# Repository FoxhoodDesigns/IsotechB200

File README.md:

# IsotechB200

This github contains the source files of the Amsterdam University of Applied Science innovationlab assignment: B-200 ADC substitution.

With the data in this repository one can recreate the design made for the project and utilize this as a Jump-off point for further development.

# CODE
Contains a sample code showing how to use the Interface with a digital Microcontroller. In this case a regular Arduino UNO.

# EAGLE
Contains Autodesk Eagle board files. Which includes circuit schematic and PCB design.

Note: For possible Eagle library dependancies please view this repository: https://github.com/FoxhoodDesigns/FHD-Libraries

# LTSPICE
Contains the LTSPICE Simulation file used for simulating the analog component of the Interface board

# doc
Contains the PDF and source LaTeX files behind the research. For documentation referencing purposes.

All work presently contained within this repository is made by the original AUAS team:
Chiel Voswijk, Kwint van den Berg and Niels Hupkens.

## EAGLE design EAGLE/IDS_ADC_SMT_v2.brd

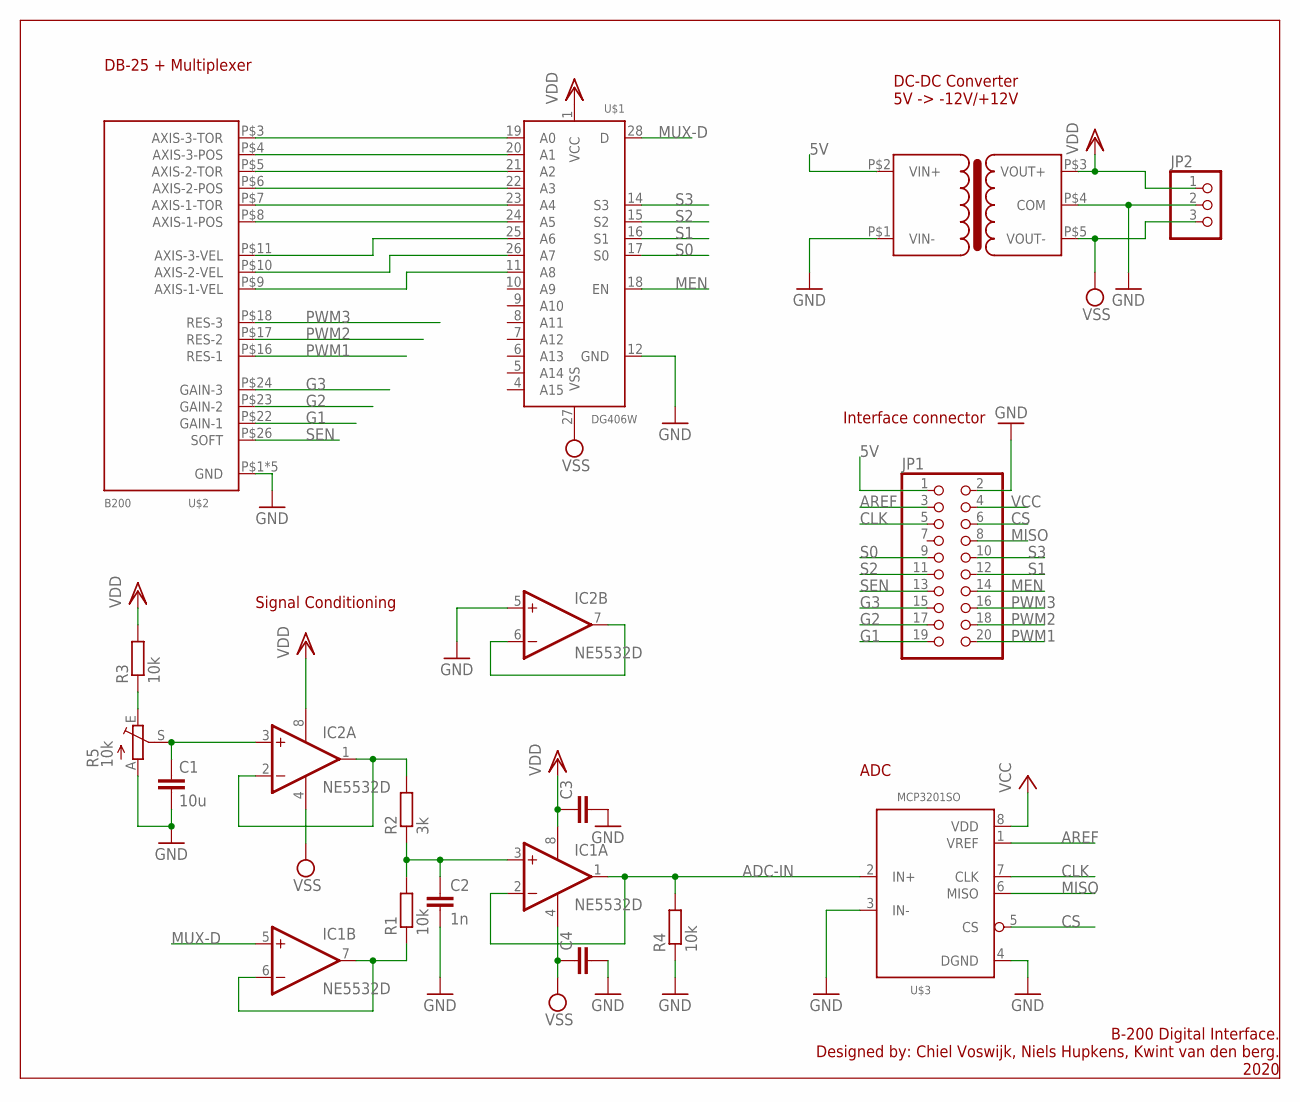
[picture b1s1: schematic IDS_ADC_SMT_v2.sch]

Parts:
C1: 10u; C1210
C2: 1n; C0805
C3, C4: C-EUC0805; C0805
IC1, IC2: NE5532D; SO08
JP1: PINHD-2X10; 2X10
JP2: PINHD-1X3; 1X03
R1, R3, R4: 10k; R0805
R2: 3k; R0805
R5: 10k; RJ9W
U$1: DG406W; SO-28W
U$2: B200; PARALLEL
U$3: MCP3201SO; SO-8
U$4: TRACO-DR-NE; TRACO-DCDC-SIP6

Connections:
5V: JP1.1, U$4.P$2 (VIN+)
ADC-IN: IC1.1 (OUT), IC1.2 (-IN), R4.2, U$3.2 (IN+)
AREF: JP1.3, U$3.1 (VREF)
CLK: JP1.5, U$3.7 (CLK)
CS: JP1.6, U$3.5 (CS)
G1: JP1.19, U$2.P$22 (GAIN-1)
G2: JP1.17, U$2.P$23 (GAIN-2)
G3: JP1.15, U$2.P$24 (GAIN-3)
GND: C1.2, C2.2, C3.2, C4.2, IC2.5 (+IN), JP1.2, JP2.2, R4.1, R5.A, U$1.12 (GND), U$2.P$1 (GND), U$2.P$2 (GND), U$2.P$19 (GND), U$2.P$20 (GND), U$2.P$21 (GND), U$3.3 (IN-), U$3.4 (DGND), U$4.P$1 (VIN-), U$4.P$4 (COM)
MEN: JP1.14, U$1.18 (EN)
MISO: JP1.8, U$3.6 (MISO)
MUX-D: IC1.5 (+IN), U$1.28 (D)
unnamed: IC2.6 (-IN), IC2.7 (OUT)
unnamed: U$1.19 (A0), U$2.P$3 (AXIS-3-TOR)
unnamed: C2.1, IC1.3 (+IN), R1.2, R2.1
unnamed: U$1.20 (A1), U$2.P$4 (AXIS-3-POS)
unnamed: IC1.6 (-IN), IC1.7 (OUT), R1.1
unnamed: U$1.21 (A2), U$2.P$5 (AXIS-2-TOR)
unnamed: IC2.1 (OUT), IC2.2 (-IN), R2.2
unnamed: C1.1, IC2.3 (+IN), R5.S
unnamed: U$1.22 (A3), U$2.P$6 (AXIS-2-POS)
unnamed: U$1.23 (A4), U$2.P$7 (AXIS-1-TOR)
unnamed: U$1.24 (A5), U$2.P$8 (AXIS-1-POS)
unnamed: U$1.25 (A6), U$2.P$11 (AXIS-3-VEL)
unnamed: U$1.26 (A7), U$2.P$10 (AXIS-2-VEL)
unnamed: U$1.11 (A8), U$2.P$9 (AXIS-1-VEL)
unnamed: R3.1, R5.E
PWM1: JP1.20, U$2.P$16 (RES-1)
PWM2: JP1.18, U$2.P$17 (RES-2)
PWM3: JP1.16, U$2.P$18 (RES-3)
S0: JP1.9, U$1.17 (S0)
S1: JP1.12, U$1.16 (S1)
S2: JP1.11, U$1.15 (S2)
S3: JP1.10, U$1.14 (S3)
SEN: JP1.13, U$2.P$26 (SOFT)
VCC: JP1.4, U$3.8 (VDD)
VDD: C3.1, IC1.8 (V+), IC2.8 (V+), JP2.1, R3.2, U$1.1 (VCC), U$4.P$3 (VOUT+)
VSS: C4.1, IC1.4 (V-), IC2.4 (V-), JP2.3, U$1.27 (VSS), U$4.P$5 (VOUT-)

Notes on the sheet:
DB-25 + Multiplexer
DC-DC Converter 5V -> -12V/+12V
ADC
Signal Conditioning
Interface connector
B-200 Digital Interface. Designed by: Chiel Voswijk, Niels Hupkens, Kwint van den berg. 2020

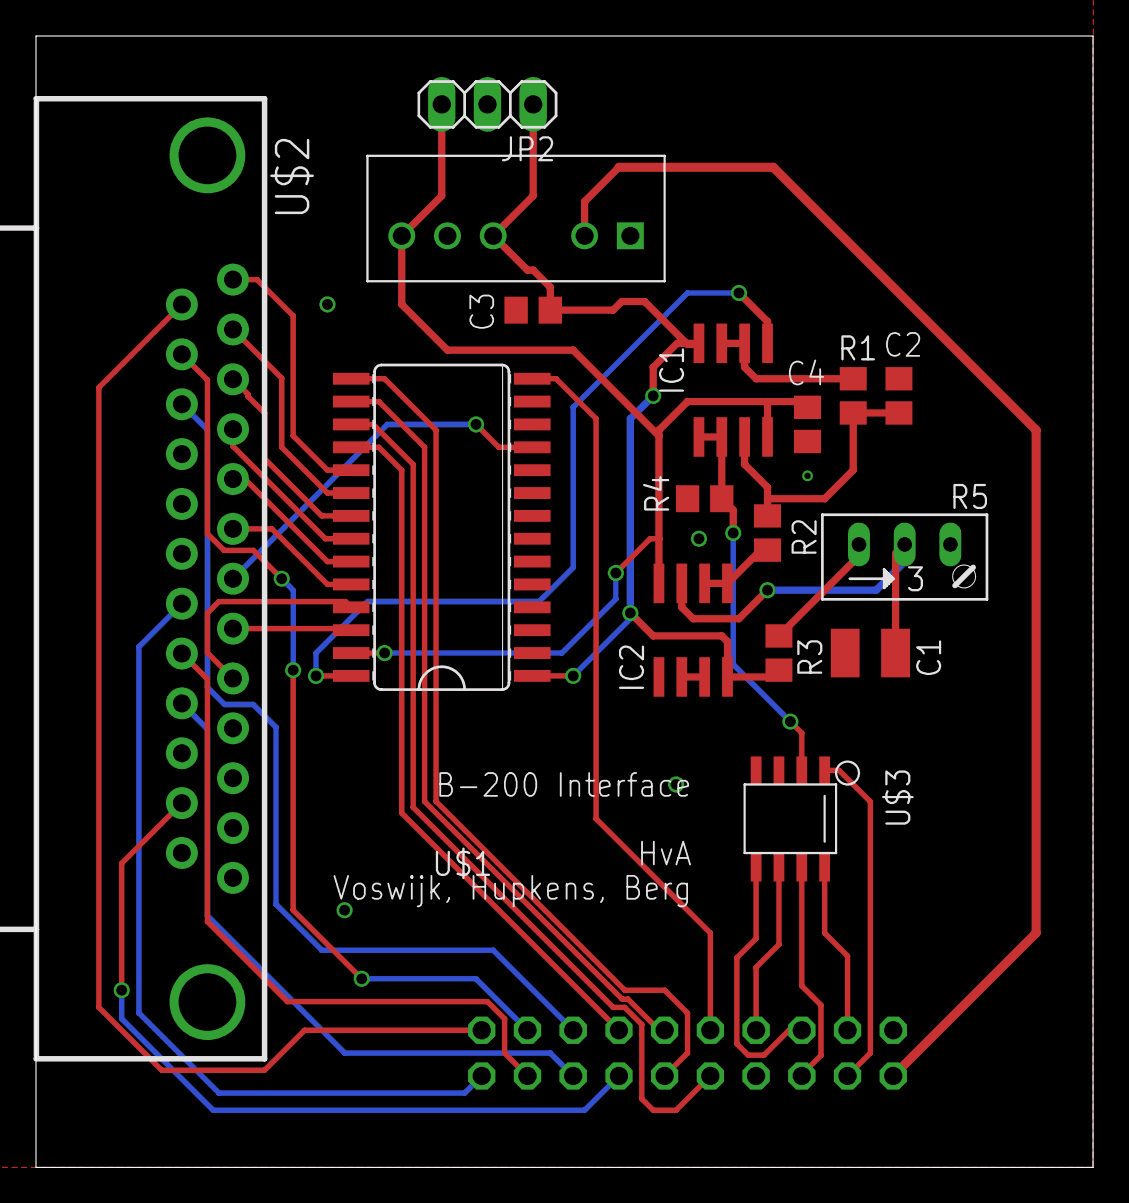
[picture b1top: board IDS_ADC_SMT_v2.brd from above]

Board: 2 copper layers, 58.7 x 62.9 mm, 17 parts (1 on the bottom side), 38 nets.

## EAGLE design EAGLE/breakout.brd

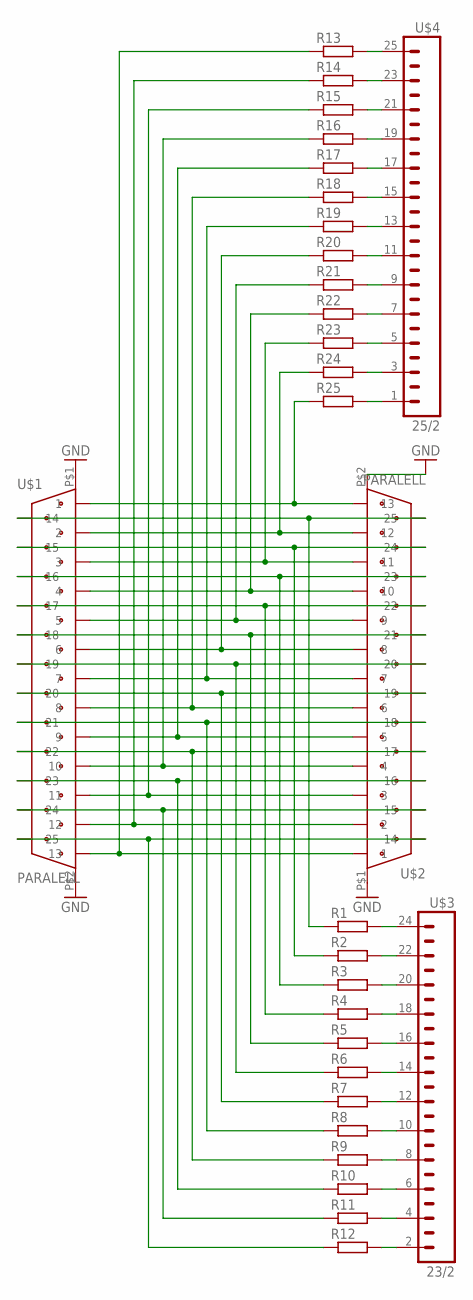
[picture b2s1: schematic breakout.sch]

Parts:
R1, R2, R3, R4, R5, R6, R7, R8, R9, R10, R11, R12, R13, R14, R15, R16, R17, R18, R19, R20, R21, R22, R23, R24, R25: R-EU_0204/7; 0204/7
U$1, U$2: PARALELL; PARALLEL
U$3: 23/2; 1X23
U$4: 25/2; 1X25

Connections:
GND: U$1.P$1, U$1.P$2, U$2.P$1, U$2.P$2
unnamed: R13.1, U$1.P$15 (13), U$2.P$3 (1)
unnamed: R14.1, U$1.P$14 (12), U$2.P$4 (2)
unnamed: R15.1, U$1.P$13 (11), U$2.P$5 (3)
unnamed: R16.1, U$1.P$12 (10), U$2.P$6 (4)
unnamed: R17.1, U$1.P$11 (9), U$2.P$7 (5)
unnamed: R18.1, U$1.P$10 (8), U$2.P$8 (6)
unnamed: R19.1, U$1.P$9 (7), U$2.P$9 (7)
unnamed: R20.1, U$1.P$8 (6), U$2.P$10 (8)
unnamed: R21.1, U$1.P$7 (5), U$2.P$11 (9)
unnamed: R22.1, U$1.P$6 (4), U$2.P$12 (10)
unnamed: R23.1, U$1.P$5 (3), U$2.P$13 (11)
unnamed: R24.1, U$1.P$4 (2), U$2.P$14 (12)
unnamed: R25.1, U$1.P$3 (1), U$2.P$15 (13)
unnamed: R1.2, U$3.24
unnamed: R2.2, U$3.22
unnamed: R3.2, U$3.20
unnamed: R4.2, U$3.18
unnamed: R5.2, U$3.16
unnamed: R6.2, U$3.14
unnamed: R7.2, U$3.12
unnamed: R8.2, U$3.10
unnamed: R9.2, U$3.8
unnamed: R10.2, U$3.6
unnamed: R11.2, U$3.4
unnamed: R12.2, U$3.2
unnamed: R13.2, U$4.25
unnamed: R14.2, U$4.23
unnamed: R15.2, U$4.21
unnamed: R16.2, U$4.19
unnamed: R17.2, U$4.17
unnamed: R18.2, U$4.15
unnamed: R19.2, U$4.13
unnamed: R20.2, U$4.11
unnamed: R21.2, U$4.9
unnamed: R22.2, U$4.7
unnamed: R23.2, U$4.5
unnamed: R24.2, U$4.3
unnamed: R25.2, U$4.1
unnamed: R1.1, U$1.P$16 (14), U$2.P$27 (25)
unnamed: R2.1, U$1.P$17 (15), U$2.P$26 (24)
unnamed: R3.1, U$1.P$18 (16), U$2.P$25 (23)
unnamed: R4.1, U$1.P$19 (17), U$2.P$24 (22)
unnamed: R5.1, U$1.P$20 (18), U$2.P$23 (21)
unnamed: R6.1, U$1.P$21 (19), U$2.P$22 (20)
unnamed: R7.1, U$1.P$22 (20), U$2.P$21 (19)
unnamed: R8.1, U$1.P$23 (21), U$2.P$20 (18)
unnamed: R9.1, U$1.P$24 (22), U$2.P$19 (17)
unnamed: R10.1, U$1.P$25 (23), U$2.P$18 (16)
unnamed: R11.1, U$1.P$26 (24), U$2.P$17 (15)
unnamed: R12.1, U$1.P$27 (25), U$2.P$16 (14)

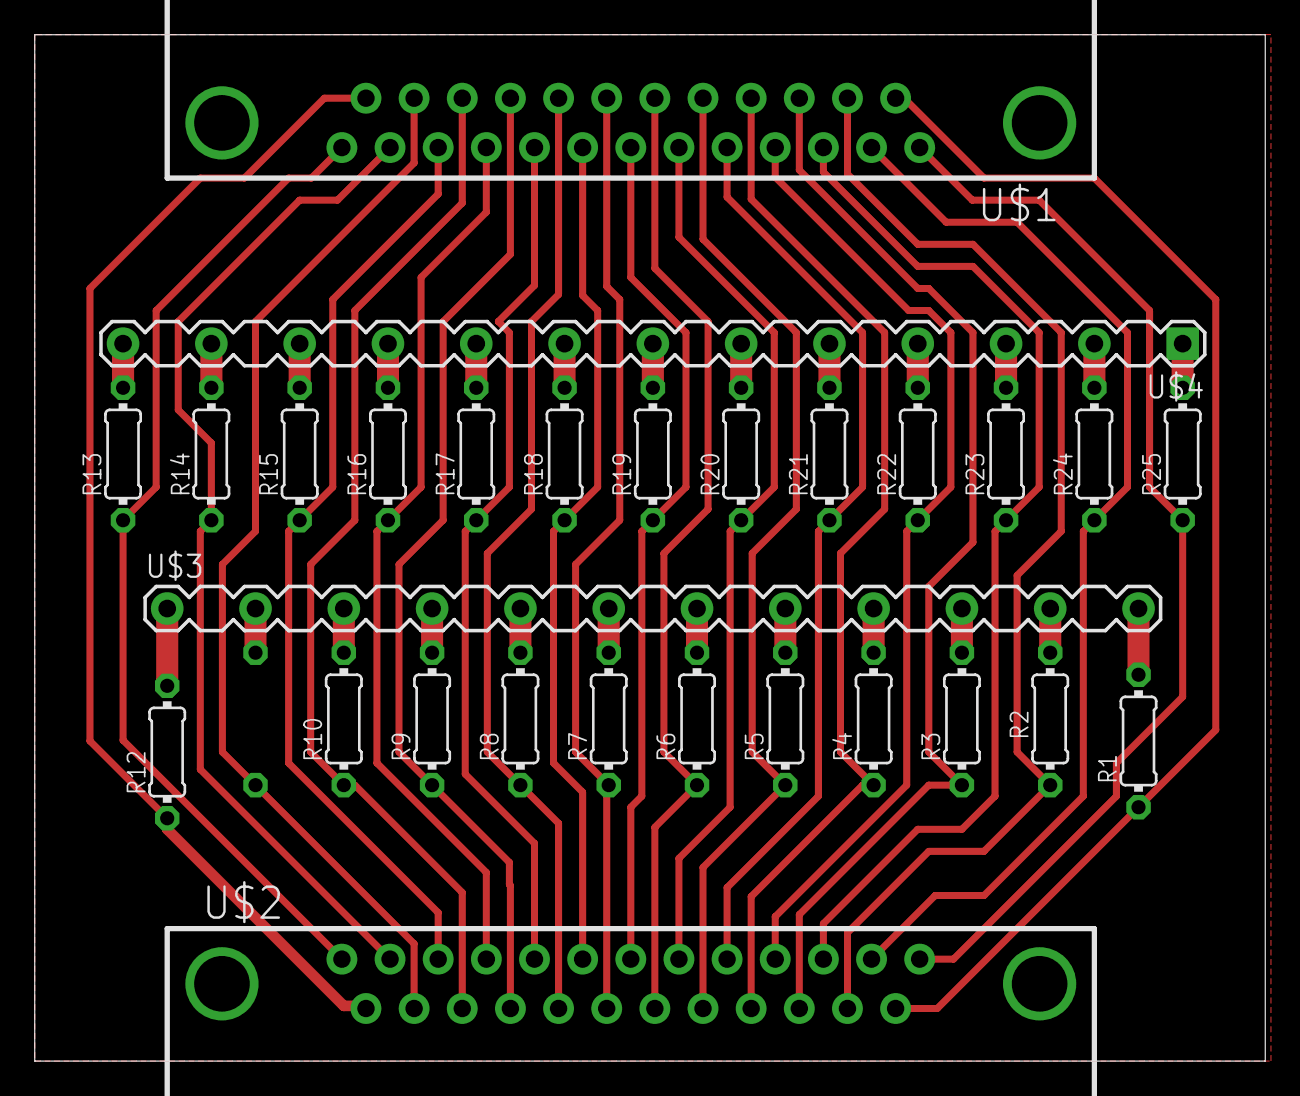
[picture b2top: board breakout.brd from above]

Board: 2 copper layers, 70.8 x 59.0 mm, 29 parts (1 on the bottom side), 51 nets.

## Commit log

2020-07-01 Initial Upload Source Material
2020-07-02 Update README.md
    Expanded Readme
2020-08-19 SMT Version Upload
    Uploaded a largely SMT design for future production.
    NOTE: Parallel port is still reversed. Pending future update.
2020-08-19 SMT Final
    Fully corrected, optimized and miniaturized SMT version of the Interface board.
